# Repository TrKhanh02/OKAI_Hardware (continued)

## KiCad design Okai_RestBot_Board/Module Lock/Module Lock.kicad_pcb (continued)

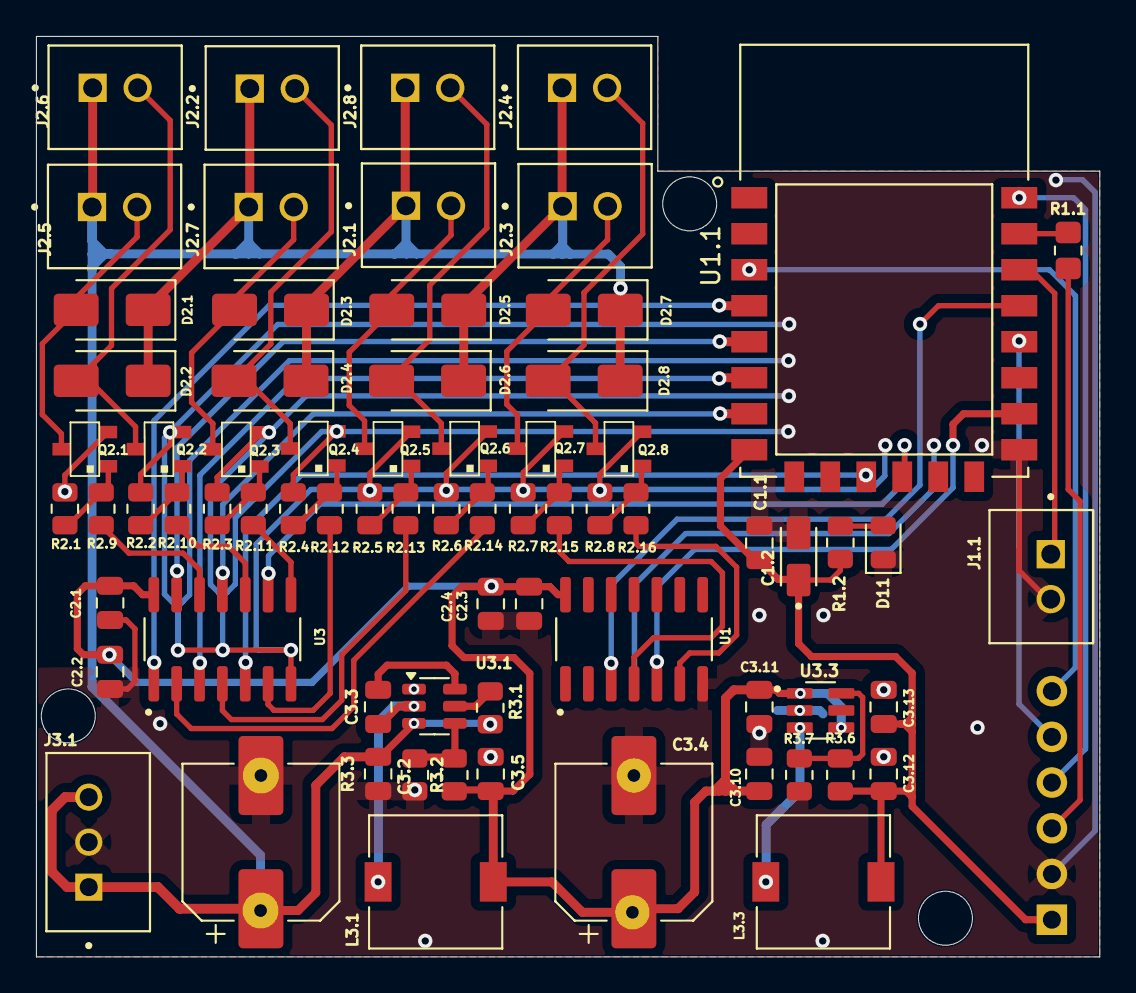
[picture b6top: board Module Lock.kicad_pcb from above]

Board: 2 copper layers, 59.1 x 51.1 mm, 73 parts (1 on the bottom side), 49 nets.
